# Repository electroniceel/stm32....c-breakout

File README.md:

STM32....C (LQFP48 and UFQFPN48) Breakout Module
================================================

A breakout module for STM32 microcontrollers in LQFP48 and UFQFPN48 footprint.

Basic Features
--------------

* Focus on small footprint and direct access to most pins.
* 40 pins broken out, organized as two single row headers in 2.54mm pitch 
* Footprints for USB-B (THT) or Micro-USB (SMT) Header
* Provides a 8 pin Micro-MaTch header for easy access to SWD and UART.
* Pushbutton for Reset (press <1 second) and starting the bootloader (press >3 seconds).
* Onboard LDO regulator (standard SOT-23-5) can be used for VDD and VDDA, just VDD or bypassed completely.
* USB VBUS (5V) is available on a pin and can be routed to the onboard LDO
* Dedicated USB disconnect function with proper pullup & disable (conforming to USB spec, not some dirty trickery)
* Use of a crystal (SMT 3.2x2.5mm) is optional.
* Options can be configured using solder bridges.
* Power LED and User LED (on PC13, PB13 or disconnected).
* Size: 25x51mm or 20x10 pins in the standard 2.54mm raster

Available pins
--------------

These pins are available on the 2.54mm headers:

* PA0 - PA12, PA15
* PB0 - PB15
* PC13 - PC15
* 5V (USB Vbus or input to the LDO regulator)
* Vdd
* Vdda
* Vbat
* NRST
* GND (2 times), also used on Vssa

These pins are also available on the Micro-MaTch:

* SWCLK, SWDIO, SWO
* NRST
* GND
* Vdd
* UART RX, UART TX (which ones can be selected via solder bridges)

These pins are not individually broken out:

* Vssa (directly connected to GND)
* PD0, PD1 (only connected to the onboard crystal pads)
* Boot0 (only connected to the reset / bootloader button)

Comparison to the popular "Blue Pill" boards
---------------------------------------------

* Allows to select the STM32 model you want, even the F4 models
* Allows to select the optimal power configuration via solder bridges
* Gives access to the bootloader via button press
* USB disconnect function allows using USB based bootloaders without hassle
* Better engineered
    * Proper ESD protection for USB
    * Ferrite beads in the power traces
    * Pads for proper decoupling caps
* Conveniant development with SWD, SWO, NRST, UART on one Micro-MaTch connector
* Possible to use THT USB-B sockets which are mechanically more stable

Downside is that it is larger, Blue Pill uses 20x7 pins raster.

Some of the supported microcontrollers
------------------------------------

* STM32F070CB
* STM32F072C8, STM32F072CB
* STM32F102C8, STM32F102CB
* STM32F103C8, STM32F103CB
* STM32F301C8
* STM32F302C8, STM32F302CB, STM32F302CC
* STM32F303C8, STM32F303CB, STM32F303CC
* STM32F334C6, STM32F334C8
* STM32F401CB, STM32F401CC, STM32F401CD, STM32F401CE
* STM32F411CC, STM32F411CE
* STM32F412CE, STM32F412CG
* STM32F413CG, STM32F413CH, STM32F423CH
* STM32L151C6-A, STM32L151C8-A, STM32L151CB-A
* STM32L152C6-A, STM32L152C8-A, STM32L152CB-A

These are just the ones that I checked for compatibility. Since ST regards pinout compatibility higly,
nearly all STM32 controllers in LQFP48 and UFQFPN48 packages should work on this board.

Schematics & Layout
-------------------

Schematics & Layout were done in KiCAD.

[Schematics as PDF](https://github.com/electroniceel/stm32....c-breakout/raw/master/schematics.pdf)

Picture
-------

License
-------

This work is licensed under a [Creative Commons Attribution 4.0 International License](https://creativecommons.org/licenses/by/4.0/).

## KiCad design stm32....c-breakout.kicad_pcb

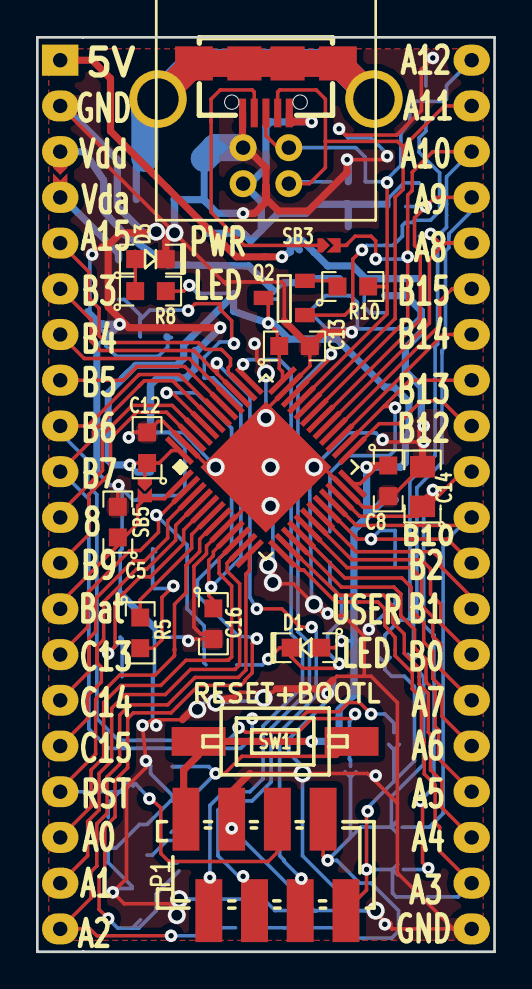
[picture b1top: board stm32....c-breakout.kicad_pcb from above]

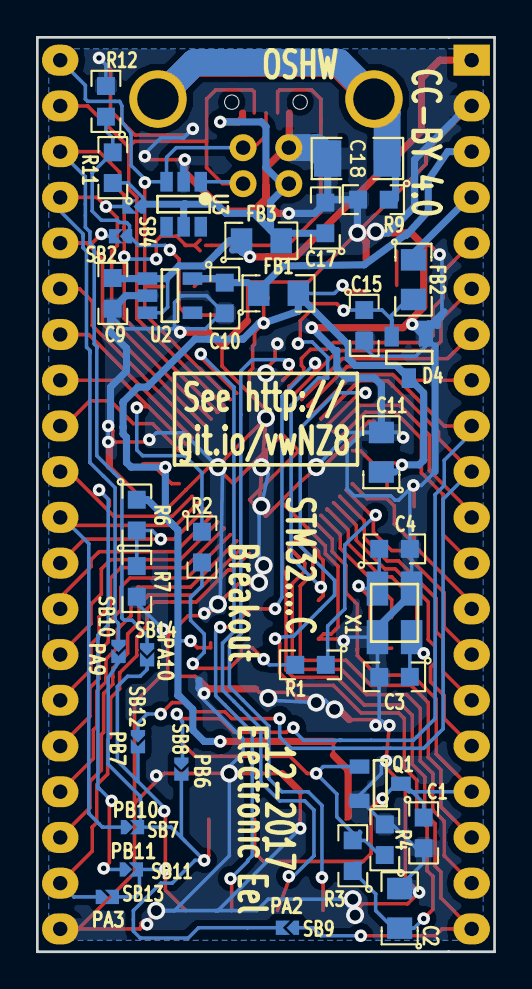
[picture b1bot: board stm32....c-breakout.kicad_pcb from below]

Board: 2 copper layers, 25.4 x 50.8 mm, 59 parts (37 on the bottom side), 57 nets.

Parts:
C1, C5, C12, C13, C14: 100n; SMD0603-wide-C
C2: 4.7µF; SMD0805-wide-C
C3, C4: 20pF; SMD0603-wide-C
C8, C11: 4.7µ; SMD0805-wide-C
C9, C10, C15: 1µ; SMD0603-wide-C
C16, C17: 10n; SMD0603-wide-C
C18: 1n 2KV; SMD1206-wide
D1: USER_LED; SMD0603-wide-diode
D3: green; SMD0603-wide-diode
D4: BAT54S; SOT-23
FB1, FB2, FB3: FILTER; SMD0805-wide
P1: MicroMatch_8pin; Conn-Micromatch-SMD-8
P2, P3: CONN_01X20; Pin_Header_Straight_1x20
P4: USB_B; USB_B-THT
P5: USB_OTG; Micro-USB-AB-receptacle-SMT
Q1: BSS138; SOT-23
Q2: BC817; SOT-23
R1, R2, R8: 1K; SMD0603-wide-R
R3: 820K; SMD0603-wide-R
R4, R6, R7, R11: 10K; SMD0603-wide-R
R5: 100R; SMD0603-wide-R
R9: 1M; SMD0603-wide-R
R10: 1.5K; SMD0603-wide-R
R12: 36K; SMD0603-wide-R
SB1: Solderbridge; Solderbridge-wide
SB2, SB3, SB4, SB5, SB7, SB8, SB9, SB10, SB11, SB12, SB13, SB14: Solderbridge
SW1: SW_PUSH; Push-Button-SMD-6.0x3.5mm
U1: STM32F103CB; QFN-48_LQFP-48_Pitch0.5mm
U2: XC6204B332MR; SOT-23-5
U3: IP4220CZ6; SOT-23-6
X1: 12MHz; smd-xtal-3225

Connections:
+3.3VADC: C15.1, C16.1, D4.2, FB2.2, U1.9
+3V3: C11.1, C12.1, C13.1, C14.1, D1.2, D4.3, FB1.2, P1.1, Q2.3, R6.1, R8.2, SB5.1, SW1.1, U1.24, U1.36, U1.48
+5V: C9.1, FB3.1, P2.1, U2.1, U2.3
/BOOT0: C2.1, R3.1, U1.44
/NRST: C1.1, P1.5, P2.17, Q1.3, U1.7
/OSC_IN: C3.1, U1.5, X1.1
/OSC_OUT: R5.1, U1.6
/PA0: P2.18, U1.10
/PA1: P2.19, U1.11
/PA2: P2.20, SB9.1, U1.12
/PA3: P3.2, SB13.1, U1.13
/PA4: P3.3, U1.14
/PA5: P3.4, U1.15
/PA6: P3.5, U1.16
/PA7: P3.6, U1.17
/PA8: P3.16, SB2.2, U1.29
/PA9: P3.17, SB4.2, SB10.1, U1.30
/PA10: P3.18, SB3.2, SB14.1, U1.31
/PA15: P2.5, U1.38
/PB0: P3.7, U1.18
/PB1: P3.8, U1.19
/PB2: P3.9, R6.2, R7.1, U1.20
/PB3/SWO: P1.6, P2.6, U1.39
/PB4: P2.7, U1.40
/PB5: P2.8, U1.41
/PB6: P2.9, SB8.1, U1.42
/PB7: P2.10, SB12.1, U1.43
/PB8: P2.11, U1.45
/PB9: P2.12, U1.46
/PB10: P3.10, SB7.1, U1.21
/PB11: C8.1, P3.11, SB11.1, U1.22
/PB12: P3.12, U1.25
/PB13: P3.13, R2.1, U1.26
/PB14: P3.14, U1.27
/PB15: P3.15, U1.28
/PC13: P2.14, R1.1, U1.2
/PC14: P2.15, U1.3
/PC15: P2.16, U1.4
/SWCLK: P1.2, U1.37
/SWDIO: P1.4, U1.34
/Switched: Q1.1, R3.2, R4.1, SW1.2
/UART_RX: P1.8, SB11.2, SB12.2, SB13.2, SB14.2
/UART_TX: P1.7, SB7.2, SB8.2, SB9.2, SB10.2
/USB_DM: P3.19, P4.2, P5.2, U1.32, U3.1
/USB_DP: P3.20, P4.3, P5.3, R10.2, U1.33, U3.3
/VBAT: C5.1, P2.13, SB5.2, U1.1
/usb/USB_DISC: Q2.1, R11.2, R12.1, SB2.1
/usb/USB_ID: P5.4, SB3.1
/usb/USB_VBUS: C17.1, FB3.2, P4.1, P5.1, R11.1, SB4.1, U3.5
GND: C1.2, C2.2, C3.2, C4.2, C5.2, C8.2, C9.2, C10.2, C11.2, C12.2, C13.2, C14.2, C15.2, C16.2, C17.2, C18.2, D3.1, D4.1, P1.3, P2.2, P3.1, P4.4, P5.5, Q1.2, R4.2, R7.2, R9.2, R12.2, U1.8, U1.23, U1.35, U1.47, U1.49, U2.2, U3.2, X1.3
unnamed: C4.1, R5.2, X1.2
unnamed: C18.1, P4.5, P5.6, R9.1
unnamed: D1.1, R1.2, R2.2
unnamed: D3.2, R8.1
unnamed: Q2.2, R10.1
Vdd_Pin: C10.1, FB1.1, P2.3, SB1.1, U2.5
Vdda_Pin: FB2.1, P2.4, SB1.2

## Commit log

2016-05-05 add gitignore and license
2016-05-05 add proper README
2018-01-04 improve readme
2018-01-04 change license to more permissive CC-BY 4.0
2018-01-04 add actual kicad files
2018-01-04 add pictures and schematics.pdf
2018-01-04 link pdf and picture in readme
2018-01-05 add size information to readme
2018-01-05 fix usb header type in readme
